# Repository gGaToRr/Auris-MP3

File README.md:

*bannière / logo ic*

# Auris — Baladeur MP3 nouvelle génération

> **Auris** est un projet étudiant dédié à la musique, pensé pour retrouver le plaisir d'un bel objet d'écoute physique, autonome et durable, enrichi par les technologies d'aujourd'hui.

---

## Sommaire

- [Présentation](#présentation)
- [Qui sommes-nous ?](#qui-sommes-nous-)
- [Pourquoi Auris ?](#pourquoi-auris-)
- [Où en sommes-nous ?](#où-en-sommes-nous-)
- [Le futur d'Auris](#le-futur-dauris)
- [Contributeurs](#contributeurs)

---

## Présentation

Auris est un projet étudiant né de la volonté de réinventer et de retrouver un support physique d'écoute musicale.

Dans un monde où le numérique évolue à grande vitesse, notre démarche consiste à intégrer les technologies actuelles au service d'un format simple, tangible et authentique. L'objectif est de permettre à chacun de **retrouver, posséder et redécouvrir sa musique ainsi que ses artistes préférés**, loin de la surconnexion et des distractions habituelles.

---

## Qui sommes-nous ?

Valentin Barrois et Pierre Untersinger sont les créateurs et fondateurs de ce projet.

Passionnés par le monde du son et de la musique, nous avons fait le choix de retourner vers un format d'écoute plus traditionnel et original. Les grandes plateformes de streaming actuelles sont devenues d'immenses structures collectant en permanence les données et les habitudes de leurs utilisateurs, un modèle dans lequel nous ne nous reconnaissons pas.

Étudiants en informatique au sein de l'école **EPITECH (campus de Marseille)**, nous mettons et mettrons l'ensemble de nos compétences au service de ce sujet qui nous anime. Nous sommes également soutenus et encouragés par notre équipe pédagogique pour mener à bien le développement d'Auris.

---

## Pourquoi Auris ?

Marre de ne plus posséder votre musique ni vos listes de lecture ? **Auris apporte une réponse concrète :**

- **Une vraie propriété de votre musique :** Vos titres et vos albums sont enregistrés directement dans la mémoire de votre matériel. Vous n'avez aucun abonnement qui expire et aucun risque de voir un morceau disparaître du jour au lendemain : vos morceaux vous appartiennent réellement.
- **Se libérer du tout-en-un du smartphone :** Aujourd'hui, notre quotidien est entièrement piloté par un seul et unique appareil, le téléphone portable (notifications, messages, réseaux sociaux). Dissocier l'écoute musicale de cet écran permet de profiter d'un moment privilégié, sans interruption.
- **Une qualité sonore fidèle et sans compromis :** Les plateformes en ligne utilisent des méthodes de compression audio pour réduire la taille des fichiers, ce qui diminue la qualité musicale originale enregistrée par les artistes. Auris est pensé pour préserver la fidélité sonore d'origine et rester compatible avec du matériel audio professionnel.
- **Un appareil presque 100 % hors-ligne :** Aucune obligation de créer un compte, aucun pistage de vos écoutes et aucune dépendance à une connexion Internet permanente pour écouter vos chansons.
- **Une conception durable et éthique :** Un baladeur résistant dans le temps, sans obsolescence programmée, conçu avec des matériaux de bonne facture et respectueux tant de l'environnement que de la main-d'œuvre lors de son cycle de fabrication.

---

## Où en sommes-nous ?

L'état d'avancement actuel du projet repose sur des bases structurées :

1. **Mise en place du dépôt GitHub :** Création de l'espace de suivi et de versionnement qui accompagnera le projet tout au long de nos études.
2. **Réalisation de la Preuve de Concept (PoC) :** Élaboration d'un premier cadre méthodologique définissant les objectifs, la faisabilité et les étapes de test nécessaires pour valider l'idée. *(Pour plus de précisions, se référer au document [poc.md](poc.md)).*
3. **Lancement de la version 0.0.1 :** Après avoir identifié l'ensemble des besoins essentiels, nous commençons le développement du logiciel interne à l'appareil (*le programme de base qui pilote directement les composants électroniques*).
4. **Prochaine étape :** La conception et les tests d'un tout premier circuit électronique de validation.

---

## Le futur d'Auris

Pour la suite, des évolutions majeures sont déjà envisagées. Elles prendront forme au fur et à mesure que le projet atteindra un niveau de maturité plus avancé :

- **Usinage et finitions soignées :** Conception d'un boîtier en pièces usinées de haute qualité, élégant et robuste.
- **Logiciel et application compagnon :** Développement d'un logiciel simple et intuitif pour faciliter le transfert et l'organisation de vos musiques depuis votre ordinateur vers l'appareil.
- **Site web et ressources :** Mise en ligne d'un site vitrine pour présenter le projet, héberger la documentation et partager des guides pratiques.
- Et bien d'autres perspectives à explorer au contact des futurs utilisateurs.

---

## Contributeurs

- Valentin Barrois
- Pierre Untersinger

---

<p align="center">
  <i>Auris — Retrouvez le lien avec votre musique.</i>
</p>

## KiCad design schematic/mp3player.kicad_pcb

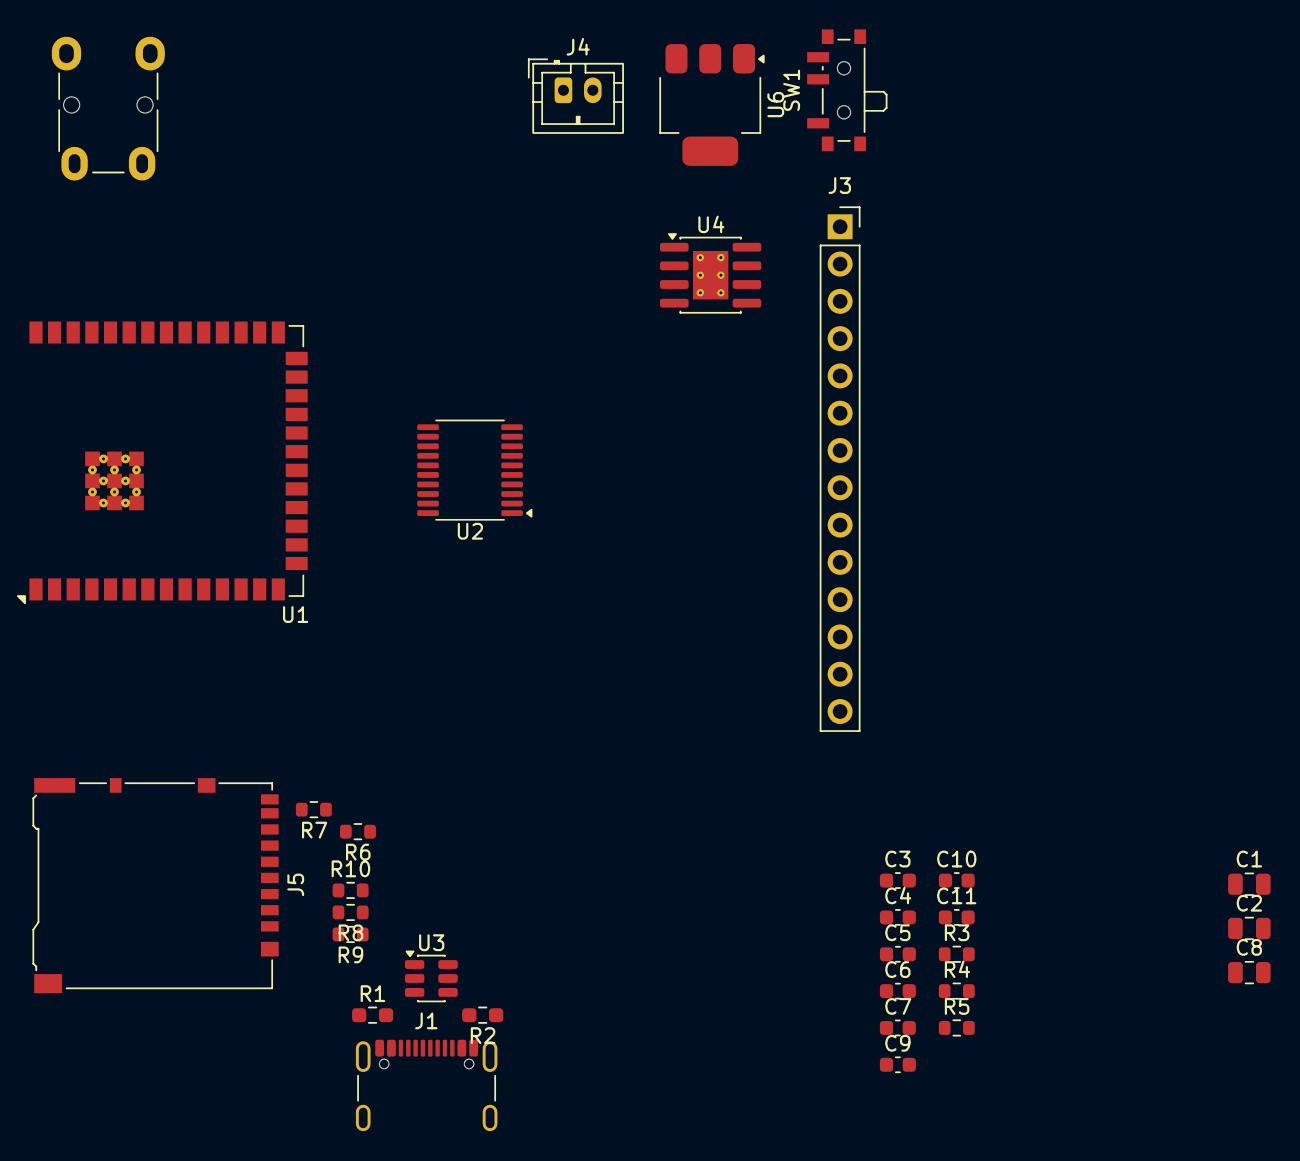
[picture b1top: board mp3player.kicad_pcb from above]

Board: 2 copper layers, 32 parts (0 on the bottom side), 38 nets, no tracks yet.

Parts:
C1, C2: 2.2 uF; C_0805_2012Metric
C3, C4, C5, C6, C7: 100 nF; C_0603_1608Metric
C8: 10 uF; C_0805_2012Metric
C9, C10: 2.2 nF; C_0603_1608Metric
C11: 1 uF; C_0603_1608Metric
J1: USB_C_Receptacle_USB2.0_16P; USB_C_Receptacle_GCT_USB4105-xx-A_16P_TopMnt_Horizontal
J2: AudioJack3; Jack_3.5mm_Lumberg_1503_07_Horizontal
J3: Conn_01x14_Socket; PinSocket_1x14_P2.54mm_Vertical
J4: Conn_01x02; JST_PH_B2B-PH-K_1x02_P2.00mm_Vertical
J5: Micro_SD_Card_Det1; microSD_HC_Hirose_DM3AT-SF-PEJM5
R1, R2: 5.1k; R_0603_1608Metric_Pad0.98x0.95mm_HandSolder
R3, R4: 470; R_0603_1608Metric
R5: R; R_0603_1608Metric
R6, R7, R8, R9, R10: 10k; R_0603_1608Metric
SW1: SW_SPDT; SW_SPDT_PCM12
U1: ESP32-S3-WROOM-2
U2: PCM5102A; TSSOP-20_4.4x6.5mm_P0.65mm
U3: USBLC6-2SC6; SOT-23-6
U4: TP4056-42-ESOP8; SOIC-8-1EP_3.9x4.9mm_P1.27mm_EP2.41x3.3mm_ThermalVias
U6: AP7361C-33E; SOT-223-3_TabPin2

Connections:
+3V3: C5.2, C6.2, C7.2, C8.2, J3.1, J5.4 (VDD), R5.1, R6.1, R7.1, R8.1, R9.1, R10.1, U1.2 (3V3), U2.1 (CPVDD), U2.8 (AVDD), U2.17 (XSMT), U2.20 (DVDD), U6.3 (VO)
/AUDIO_BCK: U1.8 (IO15), U2.13 (BCK)
/AUDIO_DIN: U1.10 (IO17), U2.14 (DIN)
/AUDIO_LRCK: U1.9 (IO16), U2.15 (LRCK)
/D+: U1.14 (USB_D+/IO20), U3.4 (I/O2)
/D-: U1.13 (USB_D-/IO19), U3.6 (I/O1)
/LDOO: C4.1, U2.18 (LDOO)
/SD_CLK: J5.5 (CLK), U1.33 (MTDO/IO40)
/SD_CMD: J5.3 (CMD), R10.2, U1.32 (MTCK/IO39)
/SD_DAT0: J5.7 (DAT0), R6.2, U1.34 (MTDI/IO41)
/SD_DAT1: J5.8 (DAT1), R7.2, U1.35 (MTMS/IO42)
/SD_DAT2: J5.1 (DAT2), R9.2, U1.24 (IO47)
/SD_DAT3: J5.2 (DAT3/CD), R8.2, U1.31 (IO38)
/SPI_MISO: J3.9, J3.13, U1.22 (IO14)
/SPI_MOSI: J3.6, J3.12, U1.21 (IO13)
/SPI_SCK: J3.7, J3.10, U1.20 (IO12)
/TFT_BL: J3.8, U1.23 (IO21)
/TFT_CS: J3.3, U1.18 (IO10)
/TFT_DC: J3.5, U1.19 (IO11)
/TFT_RESET: J3.4, U1.17 (IO9)
/TOUCH_CS: J3.11, U1.12 (IO8)
/TOUCH_IRQ: J3.14, U1.4 (IO4)
/VBAT: J4.1, SW1.2 (B), U4.5 (BAT)
/VBUS: J1.A4 (VBUS), J1.A9 (VBUS), J1.B4 (VBUS), J1.B9 (VBUS), U3.5 (VBUS), U4.4 (V_{CC}), U4.8 (CE)
/VNEG: C2.1, C3.2, U2.5 (VNEG)
GND: C2.2, C3.1, C4.2, C5.1, C6.1, C7.1, C8.1, C9.2, C10.2, C11.2, J1.A1 (GND), J1.A12 (GND), J1.B1 (GND), J1.B12 (GND), J1.SH (SHIELD), J3.2, J4.2, J5.6 (VSS), J5.SH (SHIELD), R1.1, R2.1, U1.1 (GND), U1.40 (GND), U1.41 (GND), U2.3 (CPGND), U2.9 (AGND), U2.10 (DEMP), U2.11 (FLT), U2.12 (SCK), U2.16 (FMT), U2.19 (DGND), U3.2 (GND), U4.3 (GND), U4.9 (EPAD), U6.2 (GND)
unnamed: C9.1, J2.R, R4.1
unnamed: C10.1, J2.T, R3.2
unnamed: J1.A5 (CC1), R1.2
unnamed: J1.B5 (CC2), R2.2
unnamed: J1.A6 (D+), J1.B6 (D+), U3.3 (I/O2)
unnamed: J1.A7 (D-), J1.B7 (D-), U3.1 (I/O1)
unnamed: SW1.3 (C), U6.1 (VI)
unnamed: C11.1, R5.2, U1.3 (EN)
unnamed: C1.2, U2.4 (CAPM)
unnamed: C1.1, U2.2 (CAPP)
unnamed: R3.1, U2.6 (OUTL)
unnamed: R4.2, U2.7 (OUTR)

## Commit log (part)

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2026-05-12 [init] First commit
2026-05-12 [docs] I implement the banner and the squelet of the POC
2026-05-20 [docs] I've revised the handwritten POC, but I'll need to work on it some more later.
2026-05-20 [docs] I've completed the second part of the POC. I'll go over what I've done anyway.
2026-05-20 [docs] Here, I've corrected the spelling mistakes and fixed a bug in the MD file. Part 2 is now done.
2026-05-20 [docs] I've organized the repository a bit better, with a folder dedicated to the proof of concept and another for their banner.
2026-05-20 [docs] Correction to the SVG by adding a section to indicate the current agile stage.
